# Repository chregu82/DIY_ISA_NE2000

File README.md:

# DIY_ISA_NE2000
A build yourself ISA NE2000 compatible network card based on the Realtek RTL8019AS controller.

The PCB is designed to be usable as either an 8 bit or a 16 bit ISA card. If size matters, the 16 bit part can be broken off.
All components should be solderable by hand, although the RTL8019 chip is probably challenging. The smallest resistor or cap is in a 0805 case.
There are several hardware options:
- 10BaseT
- 10Base2
- Dip switch configuration (for pre-PNP computers)
- Boot ROM
## Hardware
### PCB
PCBs can be ordered from your favourite PCB supplier, e.g. JLCPCB or PCBway by using the provided [gerber files](https://github.com/chregu82/DIY_ISA_NE2000/blob/main/PCB/gerber/gerber.zip).
### General parts (use always)
Reference | Quantity | Description | Possible source
------------ | ------------- | -------------- | --------------
C1, C2 | 2 | Capacitor 22pF, 25V, 0805 | [Mouser](https://www.mouser.com/ProductDetail/80-C0805C220K3HACTU), [Reichelt](https://www.reichelt.com/smd-vielschicht-keramikkondensator-22p-5--npo-g0805-22p-p13517.html)
C8, C10-C15 | 7 | Capacitor 0.1uF, 50V, 0805 | [Mouser](https://www.mouser.com/ProductDetail/80-C0805C104M5R), [Reichelt](https://www.reichelt.com/vielschicht-kerko-100nf-50v-125-c-kem-x7r0805-100n-p207073.html)
C17 | 1 | Capacitor 47uF, 16V, 1210 | [Mouser](https://www.mouser.com/ProductDetail/81-GRM32EC81C476KE5L), [Reichelt](https://www.reichelt.com/vielschicht-kerko-47-f-16v-85-c-kem-x5r1210-47u-p207183.html)
R1 | 1 | Resistor 27K, 0805 | [Mouser](https://www.mouser.com/ProductDetail/652-CR0805FX-2702ELF), [Reichelt](https://www.reichelt.com/smd-widerstand-0805-27-kohm-125-mw-1--smd-0805-27-0k-p32903.html)
R28, R29 | 2 | Resistor 0 Ohm, 0805 | [Mouser](https://www.mouser.com/ProductDetail/603-RC0805JR-070RL), [Reichelt](https://www.reichelt.com/smd-widerstand-0805-0-0-ohm-125-mw-rnd-0805-1-0-p212707.html)
U1 | 1 | RTL8019AS | [Aliexpress](https://www.aliexpress.com), [Utsource](https://www.utsource.net/sch/rtl8019as.html), [Reichelt](https://www.reichelt.com/de/de/voll-duplex-ethernet-kontroller-plug-play-funktion-pqfp-100-rtl-8019as-p89309.html)
U2 | 1 | EEPROM 93C46, SOIC-8 | [Mouser](https://www.mouser.com/ProductDetail/556-A93C46DNSH-B), [Reichelt](https://www.reichelt.com/eeprom-seriell-1kb-128x8-64x16-2-5--5-v-so-8-m93c46-wmn6p-p280929.html)
Y1 | 1 | Crystal 20MHz, 18pF, HC49 | [Mouser](https://www.mouser.com/ProductDetail/815-ABL-20-B2), [Reichelt](https://www.reichelt.com/standardquarz-grundton-20-mhz-iqd-lfxtal003181-p245404.html)
### 10BaseT (RJ45)
Reference | Quantity | Description | Possible source
------------ | ------------- | -------------- | --------------
C3, C4 | 2 | Capacitor 0.1uF, 50V, 0805 | [Mouser](https://www.mouser.com/ProductDetail/80-C0805C104M5R), [Reichelt](https://www.reichelt.com/vielschicht-kerko-100nf-50v-125-c-kem-x7r0805-100n-p207073.html)
C5, C6 | 2 | Capacitor 39pF, 2kV, 1206 | [Mouser](https://www.mouser.com/ProductDetail/81-GRM31A7U3D390JW1D)
R2, R3 | 2 | Resistor 470 Ohm, 0805 | [Mouser](https://www.mouser.com/ProductDetail/652-CR0805FX-4700ELF)
R4 | 1 | Resistor 200 Ohm, 0805 | [Mouser](https://www.mouser.com/ProductDetail/652-CR0805FX-2000ELF)
J2 | 1 | RJ45 Connector | [Mouser](https://www.mouser.com/ProductDetail/523-RJHSE-5481)
TR1 | 1 | LAN transformer | [Mouser](https://www.mouser.com/ProductDetail/652-PT61017PEL), [Mouser alternative part](https://www.mouser.ch/ProductDetail/815-ALANS100X12F10ET)
### 10Base2 (BNC)
Reference | Quantity | Description | Possible source
------------ | ------------- | -------------- | --------------
C7 | 1 | Capacitor 0.1uF, 50V, 0805 | [Mouser](https://www.mouser.com/ProductDetail/80-C0805C104M5R), [Reichelt](https://www.reichelt.com/vielschicht-kerko-100nf-50v-125-c-kem-x7r0805-100n-p207073.html)
C19 | 1 | Capacitor 10nF, 1kV, 1206 | [Mouser](https://www.mouser.com/ProductDetail/710-885342208021), [Reichelt](https://www.reichelt.com/ch/de/smd-kerko-1206-10-nf-1000-v-10-mlcc-rnd-1501206b1033-p226057.html)
C16, C18 | 2 | Capacitor 47uF, 16V, 1210 | [Mouser](https://www.mouser.com/ProductDetail/81-GRM32EC81C476KE5L), [Reichelt](https://www.reichelt.com/vielschicht-kerko-47-f-16v-85-c-kem-x5r1210-47u-p207183.html)
D1 | 1 | Diode BAS16, SOD-123 | [Mouser](https://www.mouser.com/ProductDetail/841-BAS16GWJ), [Reichelt](https://www.reichelt.com/gleichrichterdiode-75-v-0-215-a-sot-23-bas-16-nxp-p219347.html)
J3 | 1 | BNC Connector | [Mouser](https://www.mouser.com/ProductDetail/538-73137-5003)
Q1 | 1 | Switching Transistor NPN 600mA, SOT-23 | [Mouser](https://www.mouser.com/ProductDetail/771-PMBT2222A-T-R), [Reichelt](https://www.reichelt.com/bipolartransistor-npn-40v-0-6a-0-33w-sot-23-smbt-2222a-inf-p219350.html)
R30 | 1 | Resistor 1M, 1/2W, 0805 | [Mouser](https://www.mouser.com/ProductDetail/652-CMP0805AFX-1004L)
R21, R31 | 2 | Resistor 1K, 1% , 0805 | [Mouser](https://www.mouser.com/ProductDetail/652-CR0805FX-1001ELF), [Reichelt](https://www.reichelt.com/ch/de/smd-widerstand-0805-1-0-kohm-125-mw-1--smd-0805-1-00k-p32886.html)
R22-R25 | 4 | Resistor 510 Ohm , 0805 | [Mouser](https://www.mouser.ch/ProductDetail/652-CR0805FX-5100ELF), [Reichelt](https://www.reichelt.com/ch/de/smd-widerstand-0805-510-ohm-330-mw-1--rnd-155hp05-di-p250803.html)
R26, R27 | 2 | Resistor 270 Ohm , 0805 | [Mouser](https://www.mouser.ch/ProductDetail/652-CR0805FX-2700ELF)
TR2 | 1 | AUI Transformer | [Mouser](https://www.mouser.com/ProductDetail/673-PE-65728NL), [Mouser alternative](https://www.mouser.ch/ProductDetail/493-TG01-1006NRL)
U4 | 1 | DC-DC Converter 12V to 9V, SIP4 | [Mouser](https://www.mouser.com/ProductDetail/209-IL1209S), [Alternative Mouser, expensive](https://www.mouser.com/ProductDetail/919-RI3-1209S)
U5 | 1 | BNC Transceiver DP8392CN, DIP16 | [Aliexpress](https://www.aliexpress.com), [Utsource](https://www.utsource.net/sch/dp8392cn.html)
### Dip switches (without PNP)
Reference | Quantity | Description | Possible source
------------ | ------------- | -------------- | --------------
R5-R19 | 16 | Resistor 10K , 0805 | [Mouser](https://www.mouser.com/ProductDetail/652-CR0805-JW-103ELF), [Reichelt](https://www.reichelt.com/smd-widerstand-0805-10-kohm-125-mw-1--rnd-0805-1-10k-p183251.html)
SW1 | 1 | Dip switch 4 pos | [Mouser](https://www.mouser.com/ProductDetail/774-2104MS), [Reichelt](https://www.reichelt.com/dip-schalter-liegend-4-polig-nt-04-p13532.html)
SW2 | 1 | Dip switch 3 pos | [Mouser](https://www.mouser.com/ProductDetail/774-2103MS), [Reichelt](https://www.reichelt.com/dip-schalter-liegend-3-polig-nt-03-p36465.html)
SW3, SW5 | 2 | Dip switch 2 pos | [Mouser](https://www.mouser.com/ProductDetail/774-2102MS), [Reichelt](https://www.reichelt.com/dip-schalter-liegend-2-polig-nt-02-p36464.html)
SW4 | 1 | Dip switch 5 pos | [Mouser](https://www.mouser.com/ProductDetail/774-2105MS), [Reichelt](https://www.reichelt.com/dip-schalter-liegend-5-polig-nt-05-p36466.html)
### Boot ROM
Reference | Quantity | Description | Possible source
------------ | ------------- | -------------- | --------------
C9 | 1 | Capacitor 0.1uF, 50V, 0805 | [Mouser](https://www.mouser.com/ProductDetail/80-C0805C104M5R), [Reichelt](https://www.reichelt.com/vielschicht-kerko-100nf-50v-125-c-kem-x7r0805-100n-p207073.html)
U3 | 1 | Socket DIP32, width 15.24mm | [Mouser](https://www.mouser.com/ProductDetail/649-DILB32P223TLF), [Reichelt](https://www.reichelt.com/ic-sockel-32-polig-doppelter-federkontakt-is25t1-332b-p268816.html)
U3 | 1 | Flash 1MBit DIP32 | [Mouser](https://www.mouser.com/ProductDetail/804-39SF010A7CPHE), [Reichelt](https://www.reichelt.com/multi-nor-flash-speicher-1-mb-128-k-x-8-5-v-dip-32-39sf01070-4c-p-p266393.html)
### ISA bracket
The mounting holes in the PCB are designed for the [Keystone 9202 Bracket](https://www.mouser.ch/ProductDetail/534-9202). Holes would have to be cut into the metal. There's no drawing yet.
I designed a 3D printable [ISA bracket](https://github.com/chregu82/DIY_ISA_NE2000/tree/main/Bracket) with holes for 10BaseT and 10Base2.
### 8 bit operation
For 8 bit computers, where size matters, the 16 bit part of the PCB can be broken off. However you have to make sure that the broken off traces don't connect to anything afterwards. It is probably a good idea to cut them before braking off the PCB part.
### Soldering tips
- Flux is probably of help
- You may want to use some kind of magnification
- Check if the pins made a solid connection
- Check for solder bridges
- Go from small to big
- Always check your power rails (at the big caps) for shorts before putting it in your computer
## Programming the EEPROM
Before the card can work in your system, the RTL8019 chip needs a valid initial configuration. This can be done with the DOS tool pg8019.exe.
- Download the files from the [tools directory](https://github.com/chregu82/DIY_ISA_NE2000/tree/main/Tools)
- Make sure address 0x300 is free
- Put the networking card in a free ISA slot
- Boot to DOS
- If you want, edit 8019as.cfg according to your needs (e.g. MAC address)
- Run pg8019.exe
- Turn off your PC

After the EEPROM is programmed you should be able to use the card. Some settings could still be altered with the tool Rset8019.exe.
## Drivers
[DOS packet driver for 8 bit operation](https://github.com/chregu82/DIY_ISA_NE2000/tree/main/Drivers/8%20bit%20packet%20driver)

[DOS packet driver for 16 bit operation](https://github.com/chregu82/DIY_ISA_NE2000/tree/main/Drivers/16%20bit%20packet%20driver)

[Other drivers directly from Realtek](https://www.realtek.com/en/component/zoo/category/rtl8019as-software)

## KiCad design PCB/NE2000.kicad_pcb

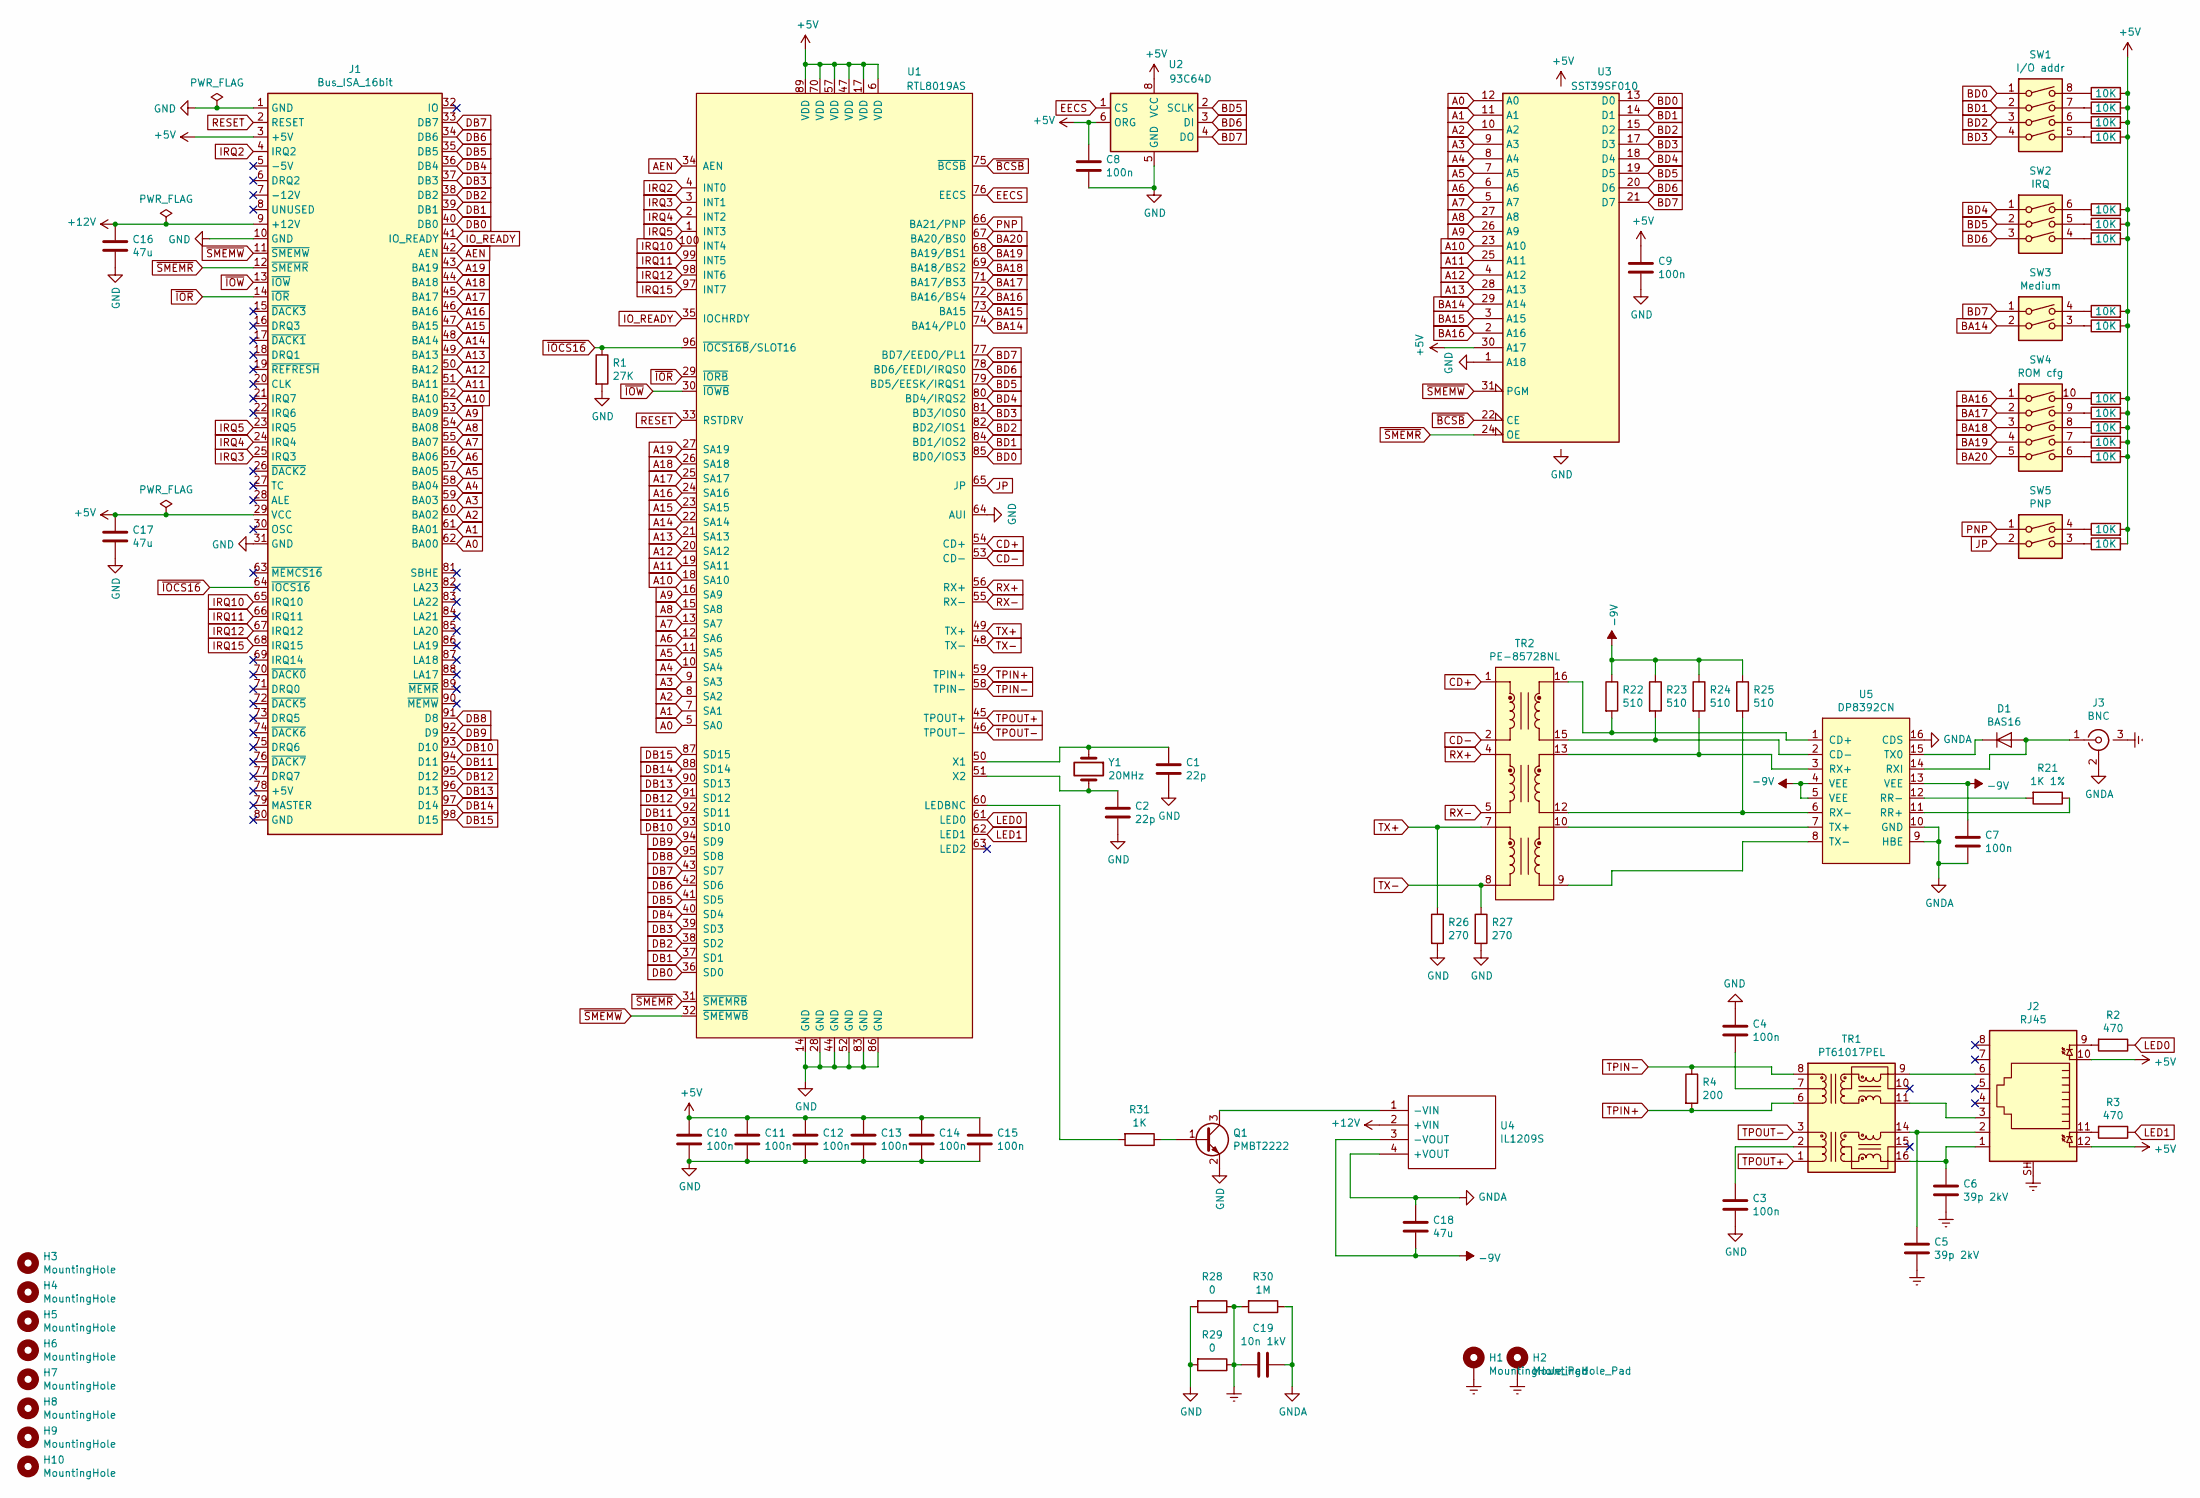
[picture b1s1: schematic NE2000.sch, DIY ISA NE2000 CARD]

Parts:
C1, C2: 22p; C_0805_2012Metric_Pad1.15x1.40mm_HandSolder; Mouser 80-C0805C220K3HACTU
C3, C4, C7, C8, C9, C10, C11, C12, C13, C14, C15: 100n; C_0805_2012Metric_Pad1.15x1.40mm_HandSolder; Mouser 80-C0805C104M5R
C5, C6: 39p 2kV; C_1206_3216Metric_Pad1.42x1.75mm_HandSolder; Mouser 81-GRM31A7U3D390JW1D
C16, C17, C18: 47u; C_1210_3225Metric_Pad1.42x2.65mm_HandSolder; Mouser 81-GRM32EC81C476KE5L
C19: 10n 1kV; C_1206_3216Metric_Pad1.42x1.75mm_HandSolder; Mouser 710-885342208021
D1: BAS16; D_SOD-123; Mouser 841-BAS16GWJ
H1, H2: MountingHole_Pad; MountingHole_3.2mm_M3_Pad_Via
H3, H4, H5, H6, H7, H8, H9, H10: MountingHole; Cutline
J1: Bus_ISA_16bit; BUS_AT_WO_SILKSCREEN
J2: RJ45; RJ45_Amphenol_RJHSE538X; Mouser 523-RJHSE-5481
J3: BNC; BNC_shield; Mouser 538-73137-5003
Q1: PMBT2222; SOT-23; Mouser 771-PMBT2222A-T/R
R1: 27K; R_0805_2012Metric_Pad1.15x1.40mm_HandSolder; Mouser 652-CR0805FX-2702ELF
R2, R3: 470; R_0805_2012Metric_Pad1.15x1.40mm_HandSolder; Mouser 652-CR0805FX-4700ELF
R4: 200; R_0805_2012Metric_Pad1.15x1.40mm_HandSolder; Mouser 652-CR0805FX-2000ELF
R5, R6, R7, R8, R9, R10, R11, R12, R13, R14, R15, R16, R17, R18, R19, R20: 10K; R_0805_2012Metric_Pad1.15x1.40mm_HandSolder; Mouser 652-CR0805-JW-103ELF
R21: 1K 1%; R_0805_2012Metric_Pad1.15x1.40mm_HandSolder; Mouser 652-CR0805FX-1001ELF
R22, R23, R24, R25: 510; R_0805_2012Metric_Pad1.15x1.40mm_HandSolder; Mouser 603-RC0805JR-07510RL
R26, R27: 270; R_0805_2012Metric_Pad1.15x1.40mm_HandSolder; Mouser 71-CRCW0805270RJNEA
R28, R29: 0; R_0805_2012Metric_Pad1.15x1.40mm_HandSolder; Mouser 603-RC0805JR-070RL
R30: 1M; R_0805_2012Metric_Pad1.15x1.40mm_HandSolder; Mouser 652-CMP0805AFX-1004L
R31: 1K; R_0805_2012Metric_Pad1.15x1.40mm_HandSolder; Mouser 652-CR0805FX-1001ELF
SW1: I/O addr; SW_DIP_SPSTx04_Slide_6.7x11.72mm_W7.62mm_P2.54mm_LowProfile; Mouser 774-2104MS
SW2: IRQ; SW_DIP_SPSTx03_Slide_6.7x9.18mm_W7.62mm_P2.54mm_LowProfile; Mouser 774-2103MS
SW3: Medium; SW_DIP_SPSTx02_Slide_6.7x6.64mm_W7.62mm_P2.54mm_LowProfile; Mouser 774-2102MS
SW4: ROM cfg; SW_DIP_SPSTx05_Slide_6.7x14.26mm_W7.62mm_P2.54mm_LowProfile; Mouser 774-2105MS
SW5: PNP; SW_DIP_SPSTx02_Slide_6.7x6.64mm_W7.62mm_P2.54mm_LowProfile; Mouser 774-2102MS
TR1: PT61017PEL; Transformer_Ethernet_Bourns_PT61017PEL; Mouser 652-PT61017PEL
TR2: PE-85728NL; Transformer_Pulse_H1100NL; Mouser 673-PE-65728NL
U1: RTL8019AS; LQFP-14x20mm_P0.5mm
U2: 93C64D; SOIC-8_3.9x4.9mm_P1.27mm; Mouser 556-A93C46DNSH-B
U3: SST39SF010; DIP32_28; Mouser 649-DILB32P223TLF
U4: IL1209S; DC_DC_12to9; Manufacturer_Part_Number IL1209S; Mouser Part Number 209-IL1209S
U5: DP8392CN; DIP-16_W7.62mm
Y1: 20MHz; Crystal_HC49-U_Vertical; Mouser 815-ABL-20-B2

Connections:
+5V: C8.1, C9.1, C10.1, C11.1, C12.1, C13.1, C14.1, C15.1, C17.1, J1.3 (+5V), J1.29 (VCC), J2.10, J2.12, R5.2, R6.2, R7.2, R8.2, R9.2, R10.2, R11.2, R12.2, R13.2, R14.2, R15.2, R16.2, R17.2, R18.2, R19.2, R20.2, U1.6 (VDD), U1.17 (VDD), U1.47 (VDD), U1.57 (VDD), U1.70 (VDD), U1.89 (VDD), U2.6 (ORG), U2.8 (VCC), U3.30 (A17), U3.32 (VCC)
+12V: C16.1, J1.9 (+12V), U4.2 (+VIN)
-9V: C7.1, C18.2, R22.1, R23.1, R24.1, R25.1, U4.3 (-VOUT), U5.4 (VEE), U5.5 (VEE), U5.13 (VEE)
A0: J1.62 (BA00), U1.5 (SA0), U3.12 (A0)
A1: J1.61 (BA01), U1.7 (SA1), U3.11 (A1)
A2: J1.60 (BA02), U1.8 (SA2), U3.10 (A2)
A3: J1.59 (BA03), U1.9 (SA3), U3.9 (A3)
A4: J1.58 (BA04), U1.10 (SA4), U3.8 (A4)
A5: J1.57 (BA05), U1.11 (SA5), U3.7 (A5)
A6: J1.56 (BA06), U1.12 (SA6), U3.6 (A6)
A7: J1.55 (BA07), U1.13 (SA7), U3.5 (A7)
A8: J1.54 (BA08), U1.15 (SA8), U3.27 (A8)
A9: J1.53 (BA09), U1.16 (SA9), U3.26 (A9)
A10: J1.52 (BA10), U1.18 (SA10), U3.23 (A10)
A11: J1.51 (BA11), U1.19 (SA11), U3.25 (A11)
A12: J1.50 (BA12), U1.20 (SA12), U3.4 (A12)
A13: J1.49 (BA13), U1.21 (SA13), U3.28 (A13)
A14: J1.48 (BA14), U1.22 (SA14)
A15: J1.47 (BA15), U1.23 (SA15)
A16: J1.46 (BA16), U1.24 (SA16)
A17: J1.45 (BA17), U1.25 (SA17)
A18: J1.44 (BA18), U1.26 (SA18)
A19: J1.43 (BA19), U1.27 (SA19)
AEN: J1.42 (AEN), U1.34 (AEN)
BA14: SW3.2, U1.74 (BA14/PL0), U3.29 (A14)
BA15: U1.73 (BA15), U3.3 (A15)
BA16: SW4.1, U1.72 (BA16/BS4), U3.2 (A16)
BA17: SW4.2, U1.71 (BA17/BS3)
BA18: SW4.3, U1.69 (BA18/BS2)
BA19: SW4.4, U1.68 (BA19/BS1)
BA20: SW4.5, U1.67 (BA20/BS0)
BD0: SW1.1, U1.85 (BD0/IOS3), U3.13 (D0)
BD1: SW1.2, U1.84 (BD1/IOS2), U3.14 (D1)
BD2: SW1.3, U1.82 (BD2/IOS1), U3.15 (D2)
BD3: SW1.4, U1.81 (BD3/IOS0), U3.17 (D3)
BD4: SW2.1, U1.80 (BD4/IRQS2), U3.18 (D4)
BD5: SW2.2, U1.79 (BD5/EESK/IRQS1), U2.2 (SCLK), U3.19 (D5)
BD6: SW2.3, U1.78 (BD6/EEDI/IRQS0), U2.3 (DI), U3.20 (D6)
BD7: SW3.1, U1.77 (BD7/EEDO/PL1), U2.4 (DO), U3.21 (D7)
CD+: TR2.1, U1.54 (CD+)
CD-: TR2.2, U1.53 (CD-)
DB0: J1.40 (DB0), U1.36 (SD0)
DB1: J1.39 (DB1), U1.37 (SD1)
DB2: J1.38 (DB2), U1.38 (SD2)
DB3: J1.37 (DB3), U1.39 (SD3)
DB4: J1.36 (DB4), U1.40 (SD4)
DB5: J1.35 (DB5), U1.41 (SD5)
DB6: J1.34 (DB6), U1.42 (SD6)
DB7: J1.33 (DB7), U1.43 (SD7)
DB8: J1.91 (D8), U1.95 (SD8)
DB9: J1.92 (D9), U1.94 (SD9)
DB10: J1.93 (D10), U1.93 (SD10)
DB11: J1.94 (D11), U1.92 (SD11)
DB12: J1.95 (D12), U1.91 (SD12)
DB13: J1.96 (D13), U1.90 (SD13)
DB14: J1.97 (D14), U1.88 (SD14)
DB15: J1.98 (D15), U1.87 (SD15)
EECS: U1.76 (EECS), U2.1 (CS)
Earth: C5.2, C6.2, C19.2, H1.1, H2.1, J2.SH, J3.3, R28.1, R29.1, R30.2
GND: C1.2, C2.2, C3.2, C4.1, C8.2, C9.2, C10.2, C11.2, C12.2, C13.2, C14.2, C15.2, C16.2, C17.2, J1.1 (GND), J1.10 (GND), J1.31 (GND), Q1.2 (E), R1.2, R26.2, R27.2, R28.2, R29.2, U1.14 (GND), U1.28 (GND), U1.44 (GND), U1.52 (GND), U1.64 (AUI), U1.83 (GND), U1.86 (GND), U2.5 (GND), U3.1 (A18), U3.16 (GND)
GNDA: C7.2, C18.1, C19.1, J3.2, R30.1, U4.4 (+VOUT), U5.9 (HBE), U5.10 (GND), U5.16 (CDS)
IO_READY: J1.41 (IO_READY), U1.35 (IOCHRDY)
IRQ2: J1.4 (IRQ2), U1.4 (INT0)
IRQ3: J1.25 (IRQ3), U1.3 (INT1)
IRQ4: J1.24 (IRQ4), U1.2 (INT2)
IRQ5: J1.23 (IRQ5), U1.1 (INT3)
IRQ10: J1.65 (IRQ10), U1.100 (INT4)
IRQ11: J1.66 (IRQ11), U1.99 (INT5)
IRQ12: J1.67 (IRQ12), U1.98 (INT6)
IRQ15: J1.68 (IRQ15), U1.97 (INT7)
JP: SW5.2, U1.65 (JP)
LED0: R2.1, U1.61 (LED0)
LED1: R3.1, U1.62 (LED1)
unnamed: C1.1, U1.50 (X1), Y1.1
unnamed: C2.1, U1.51 (X2), Y1.2
unnamed: C3.1, TR1.2 (C_TD)
unnamed: C4.2, TR1.7 (C_RD)
unnamed: C5.1, J2.2, TR1.14 (TX-)
unnamed: C6.1, J2.1, TR1.16 (TX+)
unnamed: D1.1 (K), U5.15 (TX0)
unnamed: D1.2 (A), J3.1, U5.14 (RXI)
unnamed: J2.3, TR1.11 (RX+)
unnamed: J2.6, TR1.9 (RX-)
unnamed: J2.9, R2.2
unnamed: J2.11, R3.2
unnamed: Q1.1 (B), R31.1
unnamed: Q1.3 (C), U4.1 (-VIN)
unnamed: R5.1, SW1.8
unnamed: R6.1, SW1.7
unnamed: R7.1, SW1.6
unnamed: R8.1, SW1.5
unnamed: R9.1, SW2.6
unnamed: R10.1, SW2.5
unnamed: R11.1, SW2.4
unnamed: R12.1, SW3.4
unnamed: R13.1, SW3.3
unnamed: R14.1, SW4.10
unnamed: R15.1, SW4.9
unnamed: R16.1, SW4.8
unnamed: R17.1, SW4.7
unnamed: R18.1, SW4.6
unnamed: R19.1, SW5.4
unnamed: R20.1, SW5.3
unnamed: R21.1, U5.11 (RR+)
unnamed: R21.2, U5.12 (RR-)
unnamed: R22.2, TR2.16, U5.1 (CD+)
unnamed: R23.2, TR2.15, U5.2 (CD-)
unnamed: R24.2, TR2.13, U5.3 (RX+)
unnamed: R25.2, TR2.12, U5.6 (RX-)
unnamed: R31.2, U1.60 (LEDBNC)
unnamed: TR2.9, U5.8 (TX-)
unnamed: TR2.10, U5.7 (TX+)
PNP: SW5.1, U1.66 (BA21/PNP)
RESET: J1.2 (RESET), U1.33 (RSTDRV)
RX+: TR2.4, U1.56 (RX+)
RX-: TR2.5, U1.55 (RX-)
TPIN+: R4.2, TR1.6 (RD+), U1.59 (TPIN+)
TPIN-: R4.1, TR1.8 (RD-), U1.58 (TPIN-)
TPOUT+: TR1.1 (TD+), U1.45 (TPOUT+)
TPOUT-: TR1.3 (TD-), U1.46 (TPOUT-)
TX+: R26.1, TR2.7, U1.49 (TX+)
TX-: R27.1, TR2.8, U1.48 (TX-)
~BCSB: U1.75 (~BCSB), U3.22 (CE)
~IOCS16: J1.64 (~IOCS16), R1.1, U1.96 (~IOCS16B~/SLOT16)
~IOR: J1.14 (~IOR), U1.29 (~IORB)
~IOW: J1.13 (~IOW), U1.30 (~IOWB)
~SMEMR: J1.12 (~SMEMR), U1.31 (~SMEMRB), U3.24 (OE)
~SMEMW: J1.11 (~SMEMW), U1.32 (~SMEMWB), U3.31 (PGM)

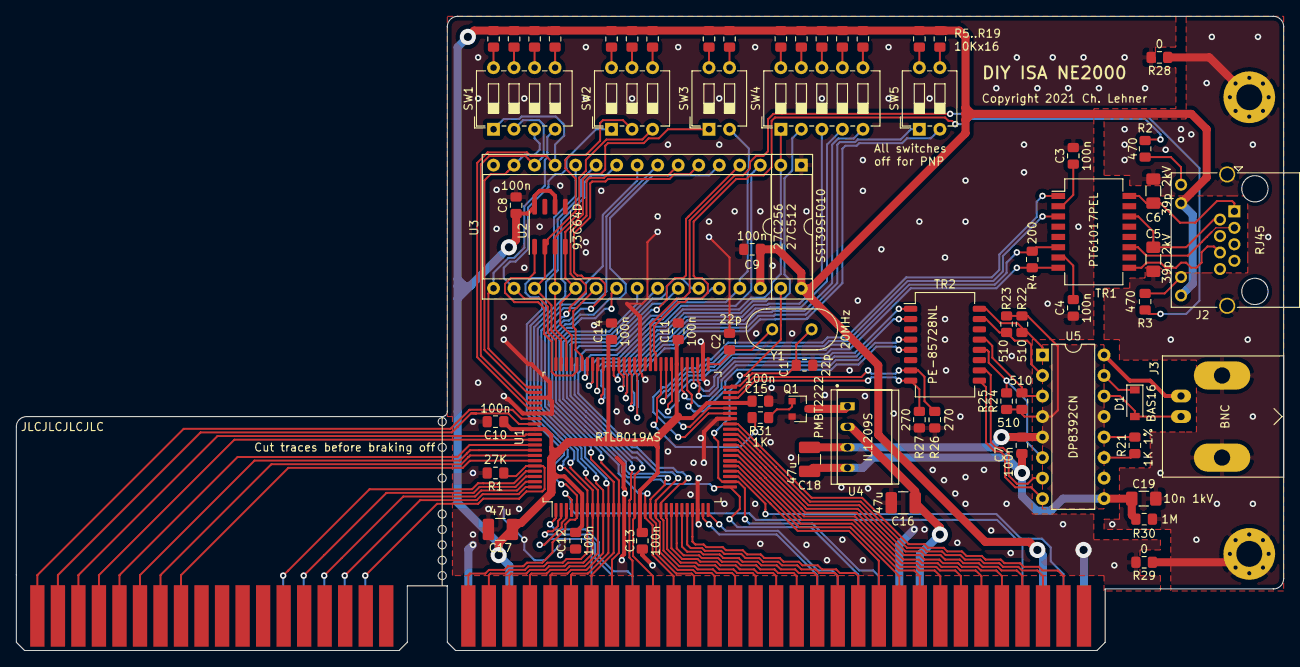
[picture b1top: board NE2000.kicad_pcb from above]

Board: 2 copper layers, 156.8 x 78.5 mm, 78 parts (0 on the bottom side), 128 nets.

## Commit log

2021-04-05 PCB work in progress
2021-04-08 Work in progress
2021-04-13 Minor changes
2021-04-25 Use different DC/DC converter
2021-04-30 Updated Gerbers
2021-05-22 Added sample boot rom
2021-05-24 Bracket V1
2021-05-24 Improved bracket
2021-07-28 Added tools, cleaned up unneeded things
2021-07-29 Description of bracket and soldering
2021-07-29 pics
2021-07-29 Documentation
2021-08-01 Added gerber zip file
2021-08-01 Added packet drivers
2021-08-01 Moved C16 and Q1 for better soldering
2021-08-01 Alternative part
2021-08-01 Parts list

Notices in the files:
PCB/NE2000.kicad_pcb:
Copyright 2021 Ch. Lehner
